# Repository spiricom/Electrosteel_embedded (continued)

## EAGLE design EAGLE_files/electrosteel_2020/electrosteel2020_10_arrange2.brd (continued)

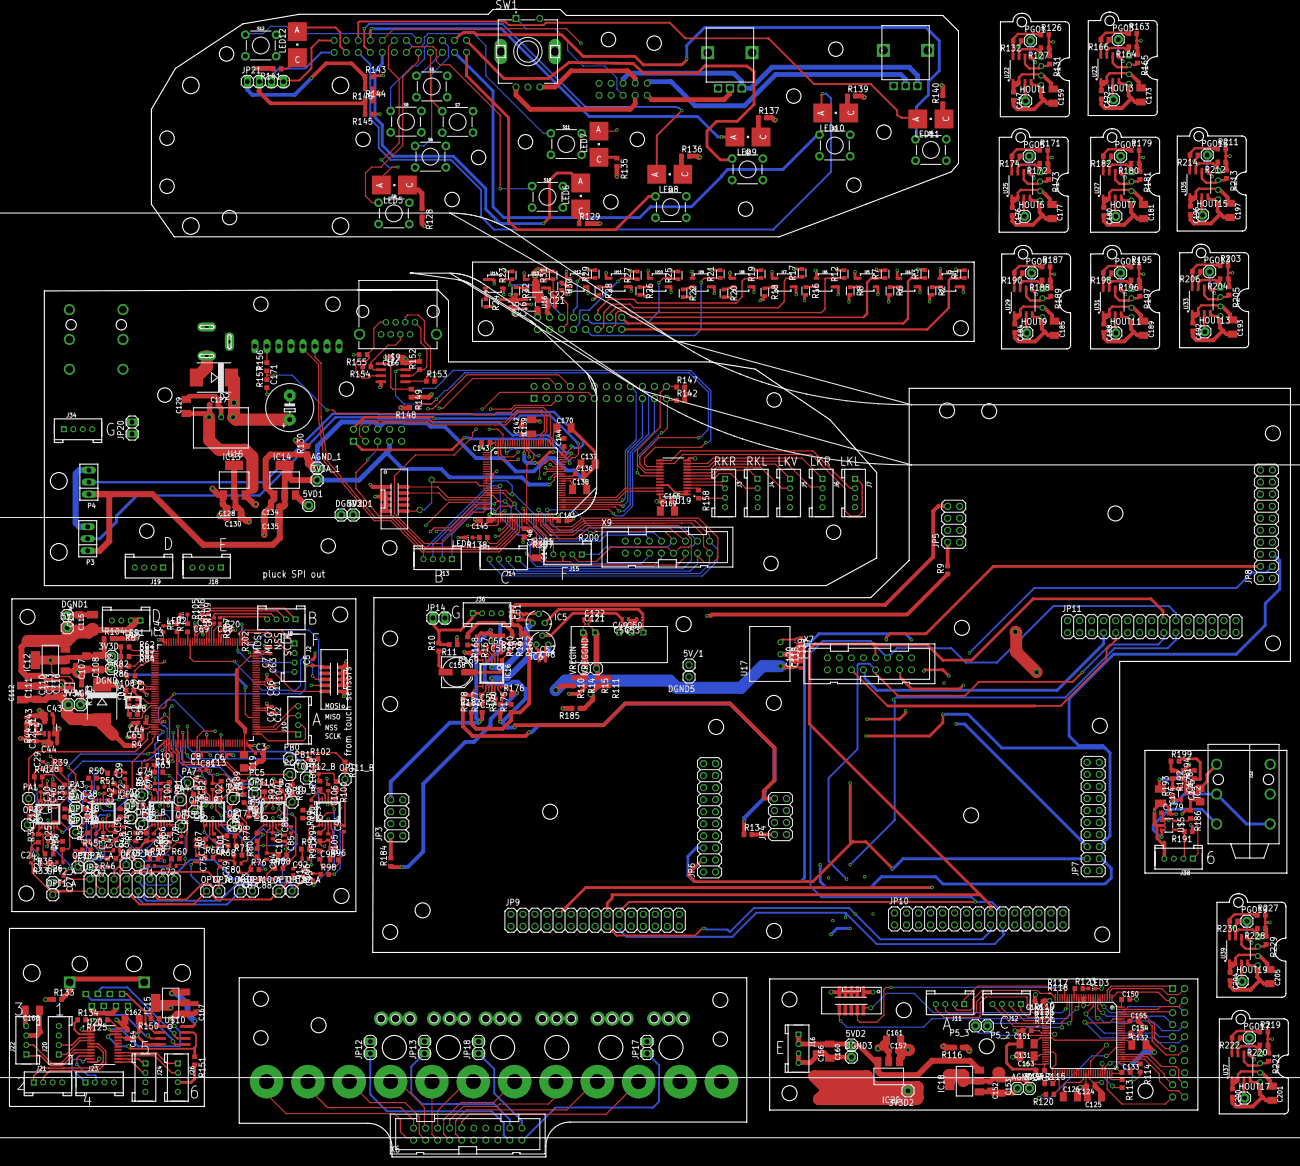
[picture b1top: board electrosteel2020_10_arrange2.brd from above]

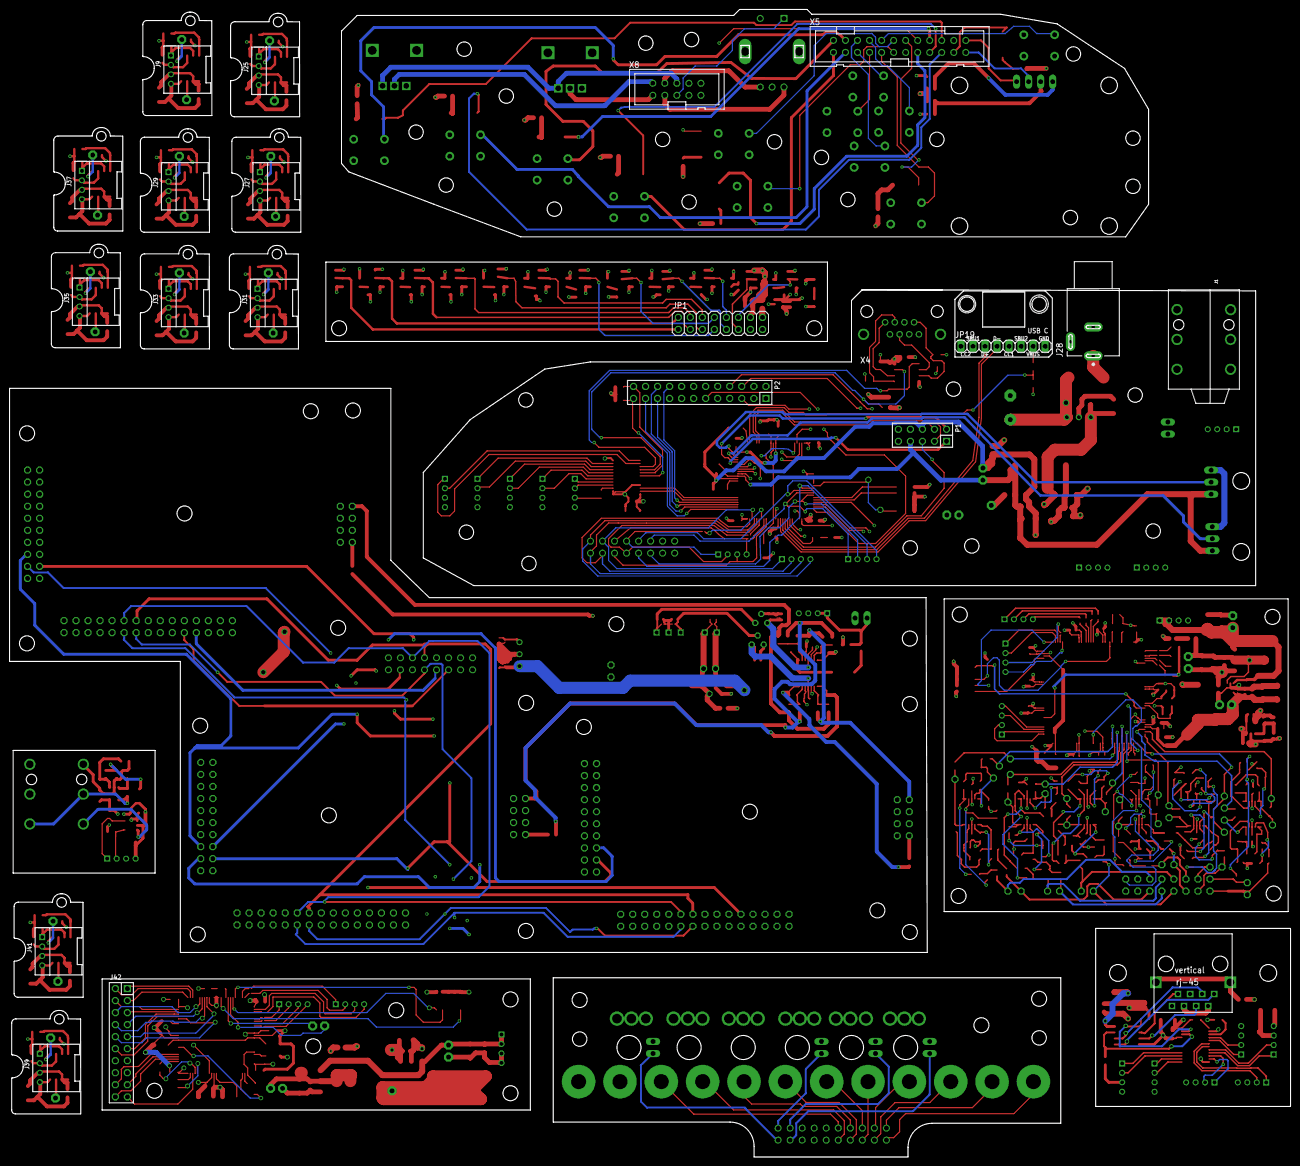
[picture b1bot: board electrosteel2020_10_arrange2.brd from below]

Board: 4 copper layers, 270.5 x 242.3 mm, 643 parts (21 on the bottom side), 495 nets.

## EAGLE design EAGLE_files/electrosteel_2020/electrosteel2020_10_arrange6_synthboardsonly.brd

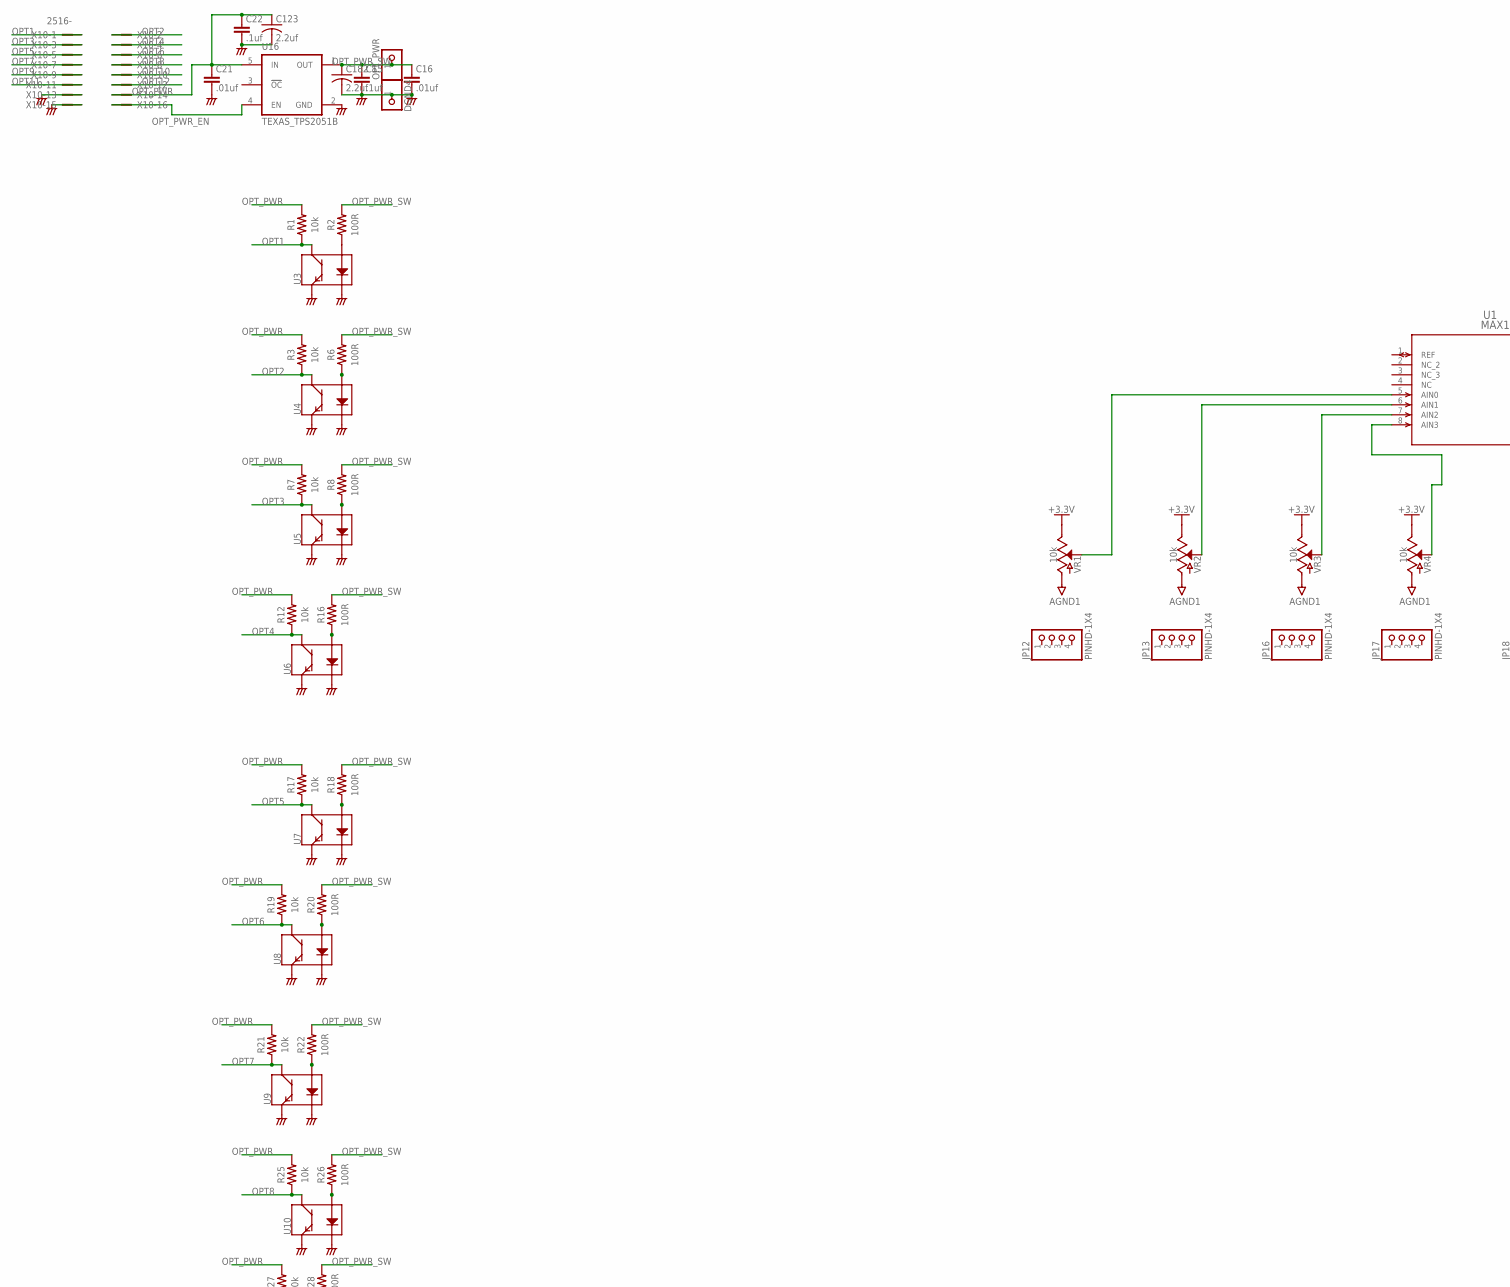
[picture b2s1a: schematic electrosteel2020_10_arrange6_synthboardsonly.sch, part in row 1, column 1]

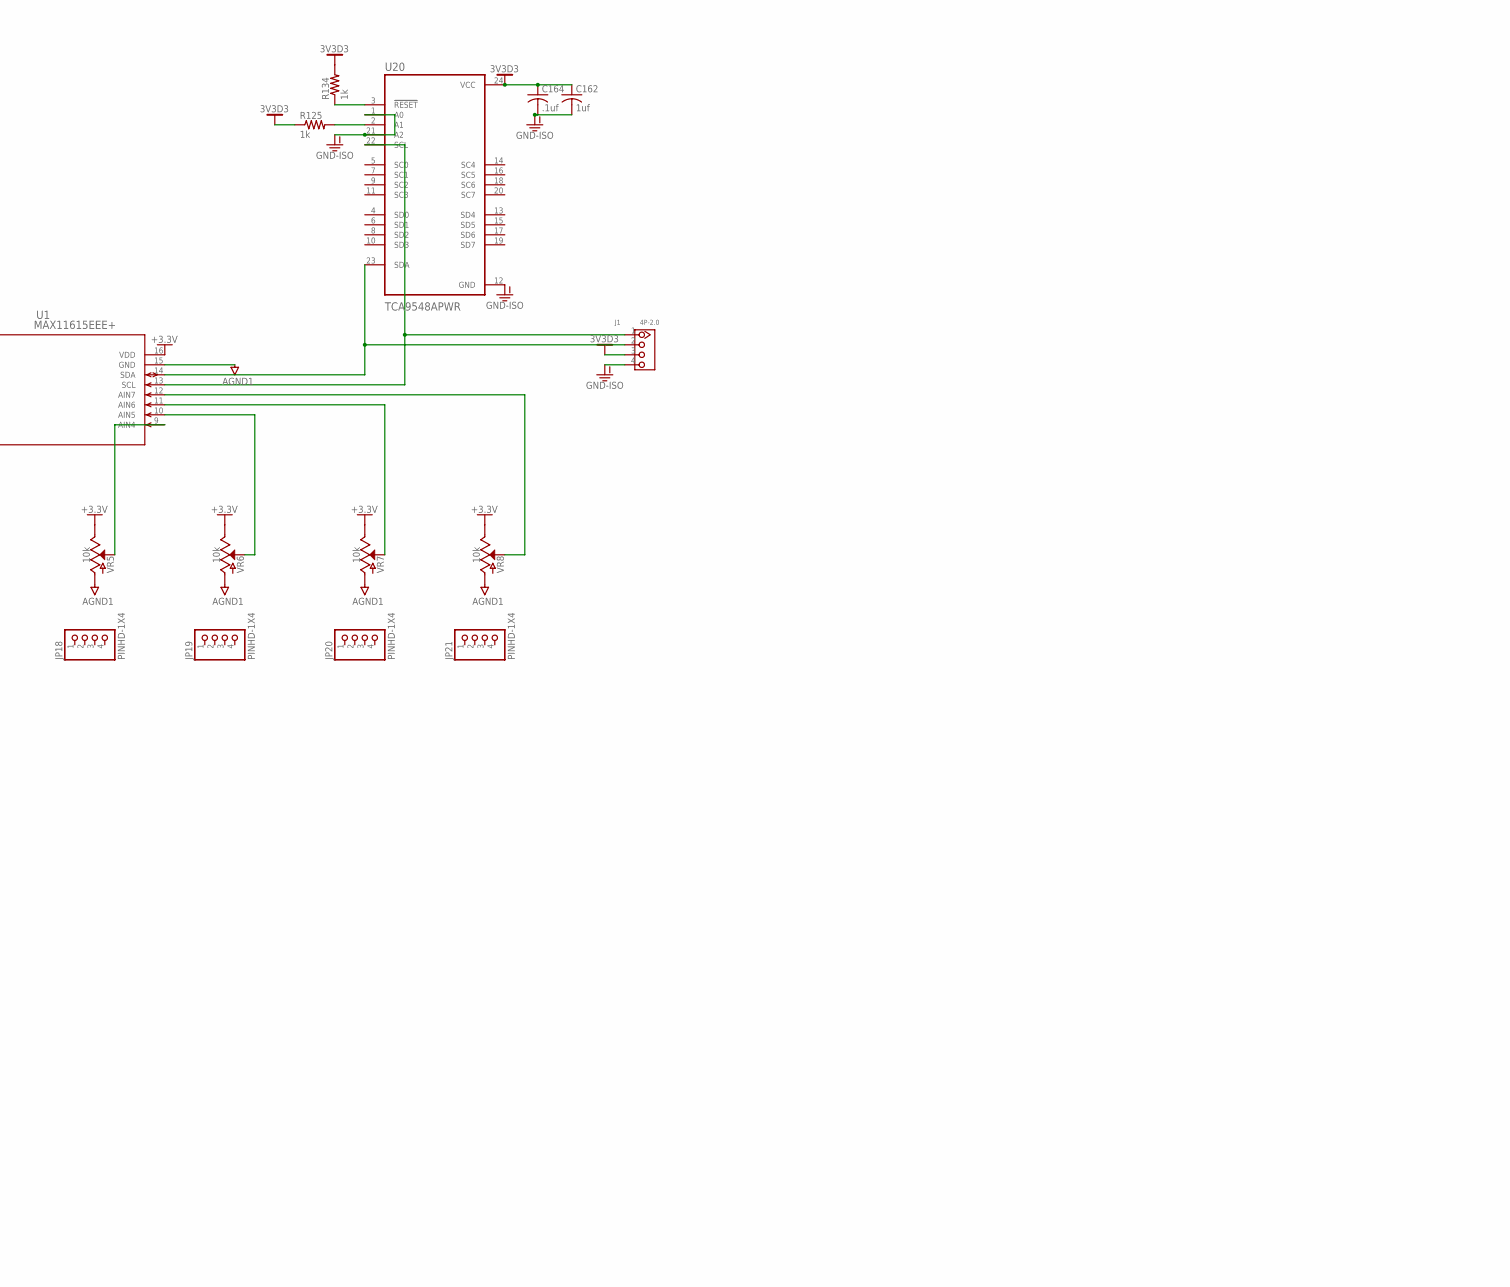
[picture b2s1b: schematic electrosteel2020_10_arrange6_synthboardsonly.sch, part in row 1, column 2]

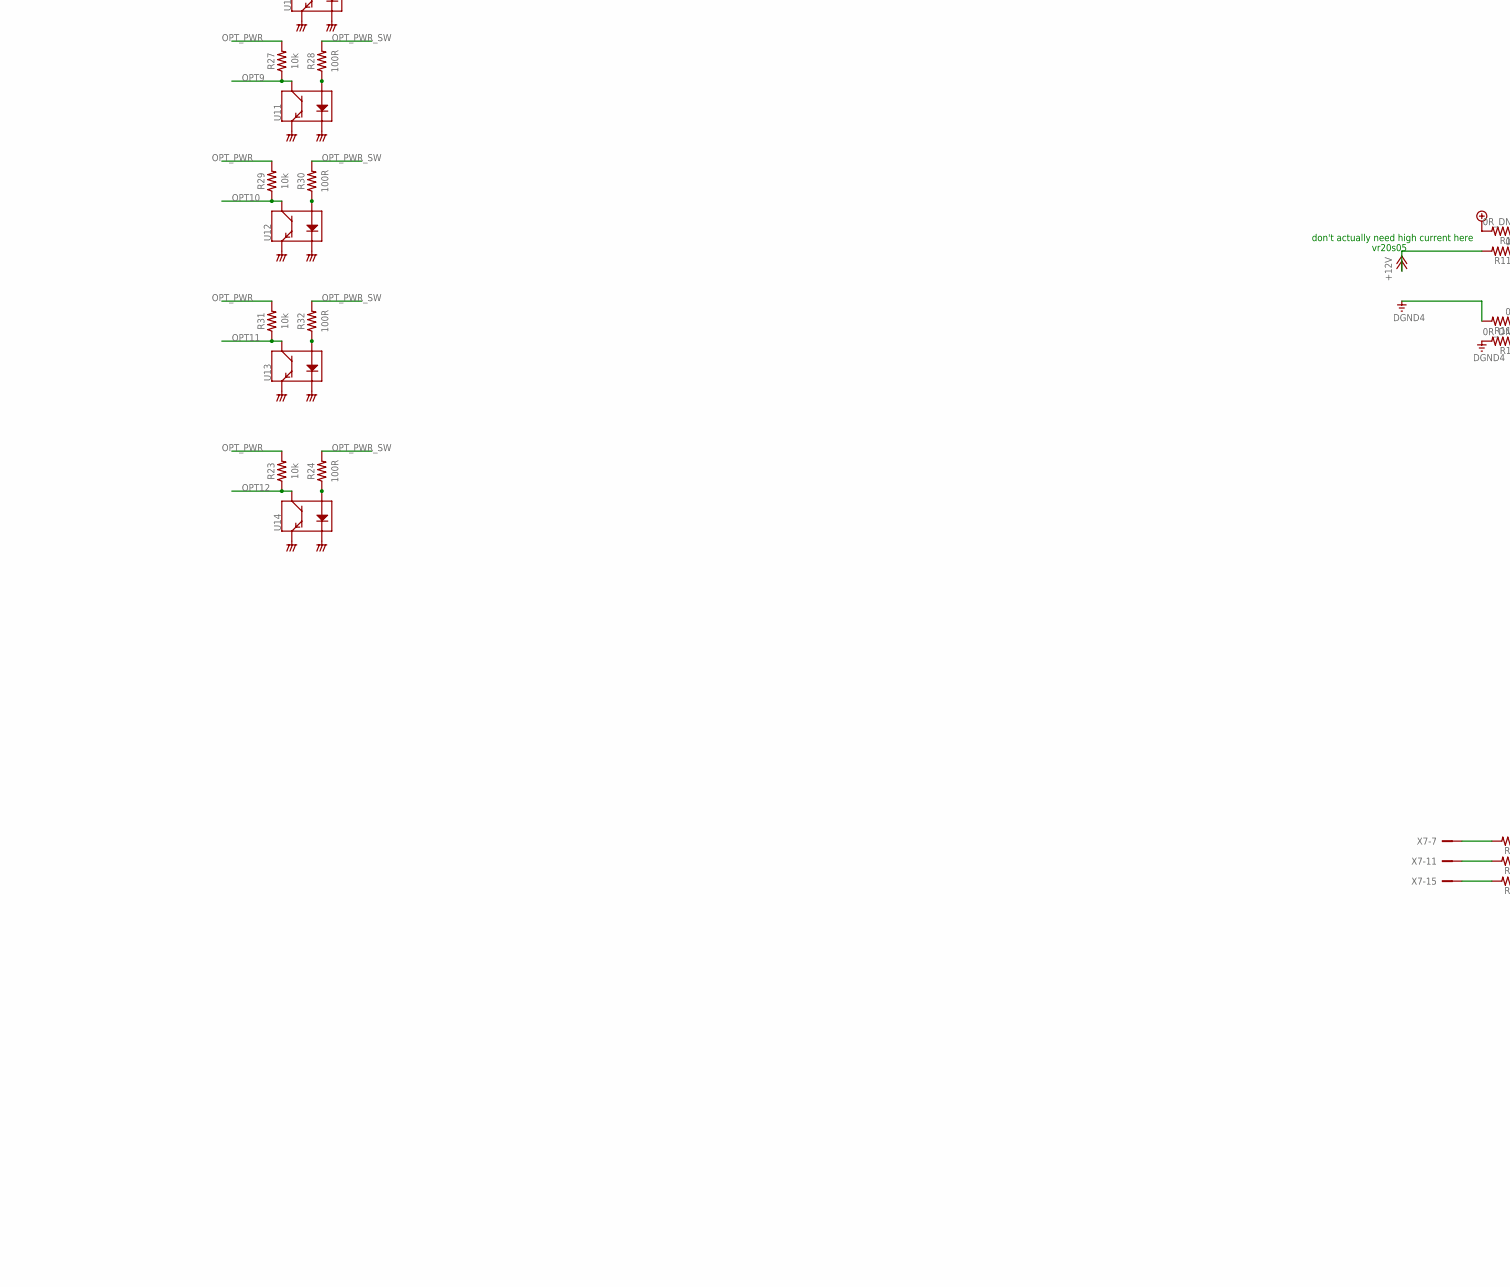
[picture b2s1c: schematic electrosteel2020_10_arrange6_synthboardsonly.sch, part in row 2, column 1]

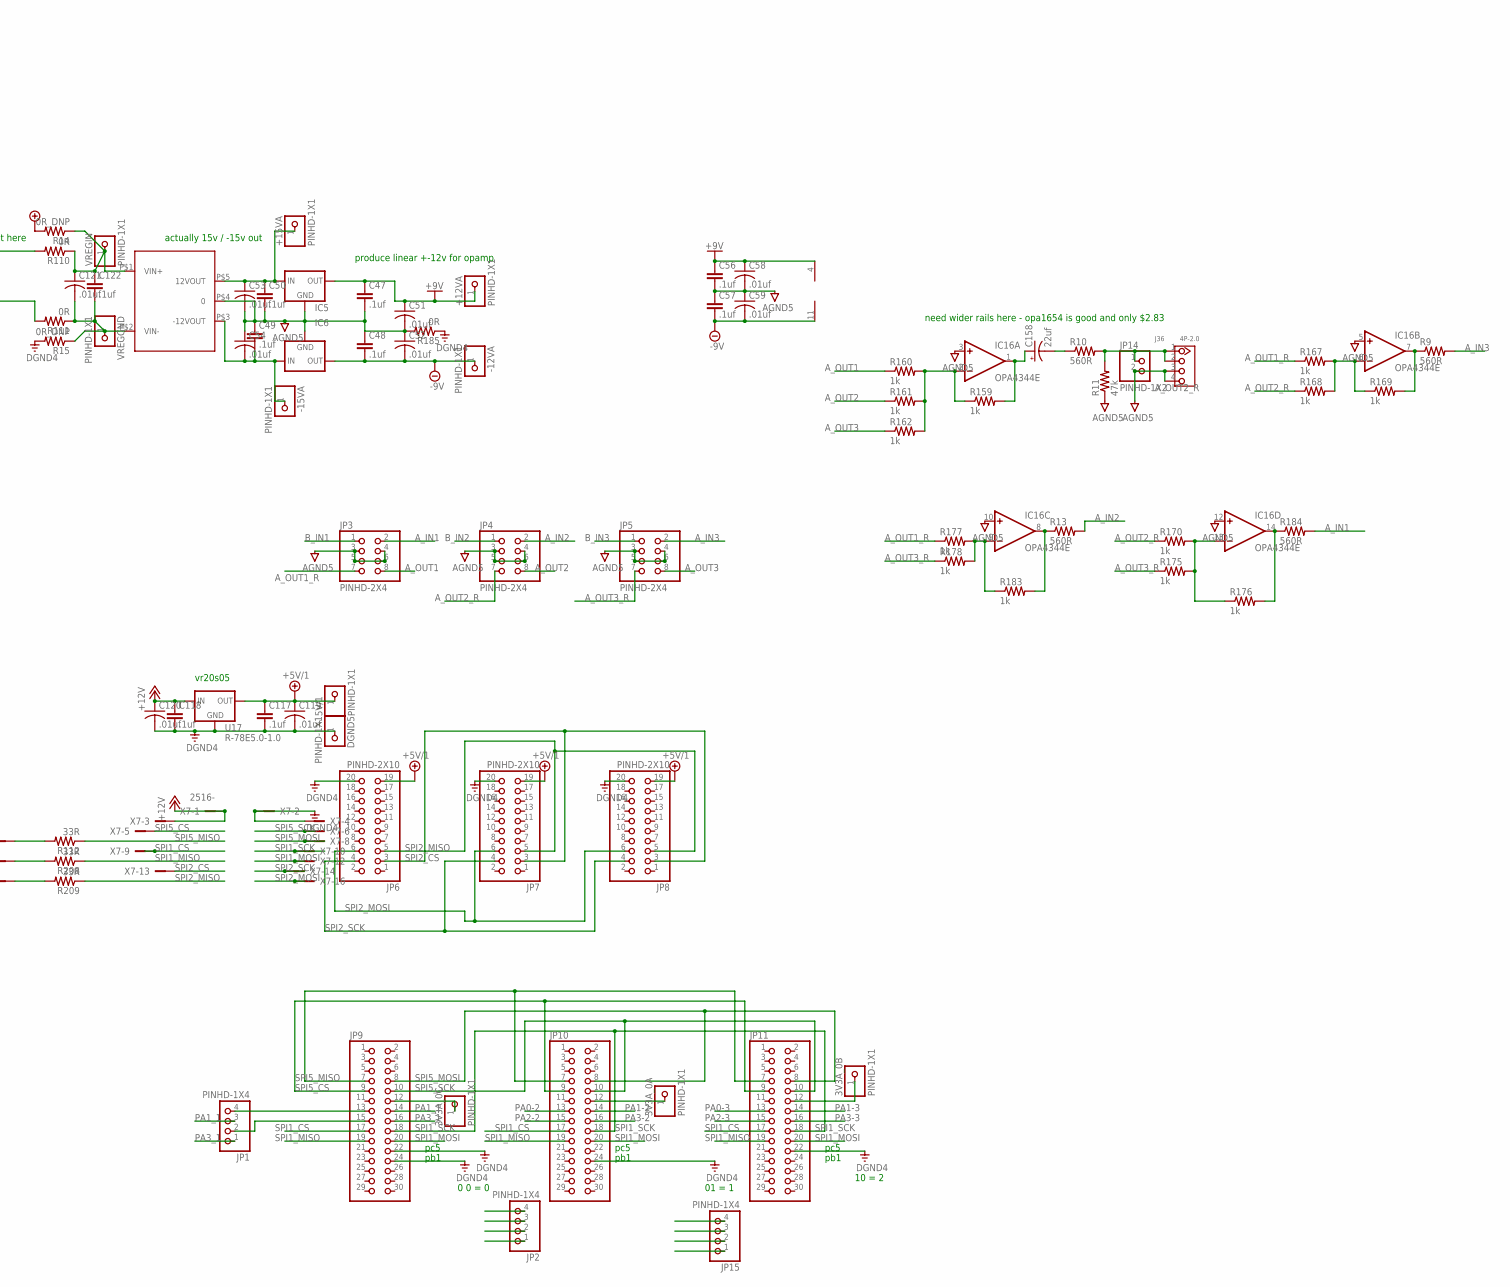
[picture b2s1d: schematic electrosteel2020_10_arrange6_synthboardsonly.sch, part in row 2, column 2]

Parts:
3V3A_0A, 3V3A_0B, 3V3A_0C, 5V/1: PINHD-1X1; 1X01; PARTNO *DNP
+12VA, +15VA: PINHD-1X1; 1X01; PARTNO *DNP
-12VA, -15VA: PINHD-1X1; 1X01; PARTNO *DNP
C15, C22, C47, C48, C49, C50, C56, C57, C117, C118, C122: .1uf; 0402; PARTNO CC0402KRX7R8BB104
C16, C21: .01uf; 0402; PARTNO CC0402KRX7R8BB103
C51, C52, C53, C54, C58, C59, C119, C120, C121: .01uf; C0201; PARTNO TMK063B7103KP-F
C123, C182: 2.2uf; C1206; PARTNO T491A225K020AT
C158: 22uf; PANASONIC_D; PARTNO EEE-1CA220NP
C162: 1uf; C1206K; PARTNO C3216X7R1E105K085AA
C164: .1uf; C0603K; PARTNO CC0603KRX7R8BB104
DGND4, DGND5: PINHD-1X1; 1X01; PARTNO *DNP
IC5: 78LXX; PARTNO LM78L12ACZ/LFT7
IC6: 79LXX; PARTNO L79L12ACZ-TR
IC16: OPA4344E; TSSOP14; PARTNO OPA1654AIPWR
J1, J36: 4P-2.0; HW4-2.0; PARTNO 110990030
JP1, JP2, JP12, JP13, JP15, JP16, JP17, JP18, JP19, JP20, JP21: PINHD-1X4; 1X04
JP3, JP4, JP5: PINHD-2X4; 2X04; PARTNO 77313-101-08LF
JP6, JP7, JP8: PINHD-2X10; 2X10; PARTNO 77313-101-20LF
JP9, JP10, JP11: PINHD-2X15; 2X15; PARTNO 77313-101-30LF
JP14: PINHD-1X2; 1X02; PARTNO *DNP
OPT_PWR: PINHD-1X1; 1X01; PARTNO *DNP
R1, R3, R7, R12, R17, R19, R21, R23, R25, R27, R29, R31: 10k; RESC1608X60; PARTNO ESR03EZPF1002
R2, R6, R8, R16, R18, R20, R22, R24, R26, R28, R30, R32: 100R; RESC1608X60; PARTNO ESR03EZPJ101
R9, R10, R13, R184: 560R; R0603; PARTNO ESR03EZPF5600
R11: 47k; R0603; PARTNO ESR03EZPJ473
R14, R15: 0R_DNP; R0603; PARTNO *DNP
R110, R111, R185: 0R; R0603; PARTNO RCS06030000Z0EA
R112, R208, R209: 33R; R0201; PARTNO RC0201FR-0733RL
R125, R134, R159, R160, R161, R162, R167, R168, R169, R170, R175, R176, R177, R178, R183: 1k; R0603; PARTNO ESR03EZPF1001
U1: MAX11615EEE+; 21-0055H_16_MXM
U3, U4, U5, U6, U7, U8, U9, U10, U11, U12, U13, U14: QRE1113; PARTNO QRE1113GR
U16: TEXAS_TPS2051B; TEXAS_SOT23-5; PARTNO TPS2051BDBVRG4
U17: R-78E5.0-1.0; DC-DC_CONVERTER_78XX; PARTNO R-78E5.0-1.0
U20: TCA9548APWR; SOP65P640X120-24N; PARTNO TCA9548APWR
U$3: CMR0512S3C; PARTNO DPU01M-15
VR1, VR2, VR3, VR4, VR5, VR6, VR7, VR8: 10k; POT-PTH-ALPS
VREGGND: PINHD-1X1; 1X01; PARTNO *DNP
VREGIN: PINHD-1X1; 1X01; PARTNO *DNP
X7, X10: 2516-; PAK100/2500-16; PARTNO D2516-6002-AR

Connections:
3V3D3: C162.1, C164.1, J1.3, R125.1, R134.2, U20.24 (VCC)
+3.3V: U1.16 (VDD), VR1.P$1 (E), VR2.P$1 (E), VR3.P$1 (E), VR4.P$1 (E), VR5.P$1 (E), VR6.P$1 (E), VR7.P$1 (E), VR8.P$1 (E)
+5V/1: 5V/1.1, C117.1, C119.1, JP6.19, JP7.19, JP8.19, R14.2, U17.VOUT (OUT)
+9V: +12VA.1, C47.1, C51.1, C56.1, C58.1, IC5.OUT, IC16.4 (V+)
+12V: C118.1, C120.1, R110.2, U17.VIN (IN), X7.1, X7.3
-9V: -12VA.1, C48.2, C52.2, C57.2, C59.2, IC6.OUT, IC16.11 (V-)
AGND1: U1.15 (GND), VR1.P$3 (A), VR2.P$3 (A), VR3.P$3 (A), VR4.P$3 (A), VR5.P$3 (A), VR6.P$3 (A), VR7.P$3 (A), VR8.P$3 (A)
AGND5: C47.2, C48.1, C49.1, C50.2, C51.2, C52.1, C53.2, C54.1, C56.2, C57.1, C58.2, C59.1, IC5.GND, IC6.GND, IC16.3 (+IN), IC16.5 (+IN), IC16.10 (+IN), IC16.12 (+IN), J36.3, J36.4, JP3.3, JP3.4, JP3.5, JP3.6, JP4.3, JP4.4, JP4.5, JP4.6, JP5.3, JP5.4, JP5.5, JP5.6, JP14.2, R11.1, R185.2, U$3.P$4 (0)
A_IN1: JP3.2, R184.2
A_IN2: JP4.2, R13.2
A_IN3: JP5.2, R9.2
A_OUT1: JP3.8, R160.1
A_OUT1_R: JP3.7, R167.1, R177.1
A_OUT2: JP4.8, R161.1
A_OUT2_R: JP4.7, R168.1, R170.1
A_OUT3: JP5.8, R162.1
A_OUT3_R: JP5.7, R175.1, R178.1
B_IN1: JP3.1
B_IN2: JP4.1
B_IN3: JP5.1
CGND: C15.2, C16.2, C21.2, C22.2, C123.2, C182.2, DGND4.1, U3.2 (K), U3.4 (E), U4.2 (K), U4.4 (E), U5.2 (K), U5.4 (E), U6.2 (K), U6.4 (E), U7.2 (K), U7.4 (E), U8.2 (K), U8.4 (E), U9.2 (K), U9.4 (E), U10.2 (K), U10.4 (E), U11.2 (K), U11.4 (E), U12.2 (K), U12.4 (E), U13.2 (K), U13.4 (E), U14.2 (K), U14.4 (E), U16.2 (GND), X10.13, X10.15
DGND4: C117.2, C118.2, C119.2, C120.2, DGND5.1, JP6.20, JP7.20, JP8.20, JP9.22, JP9.24, JP10.24, JP11.22, R15.2, R111.2, R185.1, U17.GND, X7.2, X7.4
GND-ISO: C162.2, C164.2, J1.4, U20.1 (A0), U20.12 (GND), U20.21 (A2)
unnamed: R6.1, U4.1 (A)
unnamed: R2.1, U3.1 (A)
unnamed: U1.5 (AIN0), VR1.P$2 (S)
unnamed: U1.6 (AIN1), VR2.P$2 (S)
unnamed: U1.7 (AIN2), VR3.P$2 (S)
unnamed: U1.8 (AIN3), VR4.P$2 (S)
unnamed: R8.1, U5.1 (A)
unnamed: U1.9 (AIN4), VR5.P$2 (S)
unnamed: U1.10 (AIN5), VR6.P$2 (S)
unnamed: IC16.6 (-IN), R167.2, R168.2, R169.1
unnamed: U1.11 (AIN6), VR7.P$2 (S)
unnamed: U1.12 (AIN7), VR8.P$2 (S)
unnamed: J1.2, U1.14 (SDA), U20.23 (SDA)
unnamed: J1.1, U1.13 (SCL), U20.22 (SCL)
unnamed: R125.2, U20.2 (A1)
unnamed: IC16.2 (-IN), R159.1, R160.2, R161.2, R162.2
unnamed: IC16.7 (OUT), R9.1, R169.2
unnamed: IC16.9 (-IN), R177.2, R178.2, R183.1
unnamed: +15VA.1, C50.1, C53.1, IC5.IN, U$3.P$5 (12VOUT)
unnamed: C158.+, IC16.1 (OUT), R159.2
unnamed: R16.1, U6.1 (A)
unnamed: -15VA.1, C49.2, C54.2, IC6.IN, U$3.P$3 (-12VOUT)
unnamed: R18.1, U7.1 (A)
unnamed: R20.1, U8.1 (A)
unnamed: R22.1, U9.1 (A)
unnamed: R24.1, U14.1 (A)
unnamed: R26.1, U10.1 (A)
unnamed: R28.1, U11.1 (A)
unnamed: R30.1, U12.1 (A)
unnamed: R32.1, U13.1 (A)
unnamed: C121.2, C122.2, R15.1, R111.1, U$3.P$2 (VIN-), VREGGND.1
unnamed: C121.1, C122.1, R14.1, R110.1, U$3.P$1 (VIN+), VREGIN.1
unnamed: R134.1, U20.3 (!RESET)
unnamed: IC16.8 (OUT), R13.1, R183.2
unnamed: C158.-, R10.1
unnamed: IC16.14 (OUT), R176.2, R184.1
unnamed: IC16.13 (-IN), R170.2, R175.2, R176.1
unnamed: J36.1, J36.2, JP14.1, R10.2, R11.2
unnamed: R209.2, X7.15
unnamed: R208.2, X7.11
unnamed: R112.2, X7.7
unnamed: JP1.4, JP9.13
unnamed: 3V3A_0C.1, JP9.12
unnamed: JP1.2, JP9.15
unnamed: 3V3A_0A.1, JP10.12
unnamed: 3V3A_0B.1, JP11.12
OPT1: R1.1, U3.3 (C), X10.1
OPT2: R3.1, U4.3 (C), X10.2
OPT3: R7.1, U5.3 (C), X10.3
OPT4: R12.1, U6.3 (C), X10.4
OPT5: R17.1, U7.3 (C), X10.5
OPT6: R19.1, U8.3 (C), X10.6
OPT7: R21.1, U9.3 (C), X10.7
OPT8: R25.1, U10.3 (C), X10.8
OPT9: R27.1, U11.3 (C), X10.9
OPT10: R29.1, U12.3 (C), X10.10
OPT11: R31.1, U13.3 (C), X10.11
OPT12: R23.1, U14.3 (C), X10.12
OPT_PWR: C21.1, C22.1, C123.1, R1.2, R3.2, R7.2, R12.2, R17.2, R19.2, R21.2, R23.2, R25.2, R27.2, R29.2, R31.2, U16.5 (IN), X10.14
OPT_PWR_EN: U16.4 (EN), X10.16
OPT_PWR_SW: C15.1, C16.1, C182.1, OPT_PWR.1, R2.2, R6.2, R8.2, R16.2, R18.2, R20.2, R22.2, R24.2, R26.2, R28.2, R30.2, R32.2, U16.1 (OUT)
PA0-2: JP2.4, JP10.13
PA0-3: JP11.13, JP15.4
PA1-2: JP2.3, JP10.14
PA1-3: JP11.14, JP15.3
PA1_1: JP1.3, JP9.14
PA2-2: JP2.2, JP10.15
PA2-3: JP11.15, JP15.2
PA3-2: JP2.1, JP10.16
PA3-3: JP11.16, JP15.1
PA3_1: JP1.1, JP9.16
SPI1_CS: JP9.17, JP10.17, JP11.17, X7.9
SPI1_MISO: JP9.19, JP10.19, JP11.19, R208.1
SPI1_MOSI: JP9.20, JP10.20, JP11.20, X7.12
SPI1_SCK: JP9.18, JP10.18, JP11.18, X7.10
SPI2_CS: JP6.3, JP7.3, JP8.3, X7.13
SPI2_MISO: JP6.5, JP7.5, JP8.5, R209.1
SPI2_MOSI: JP6.6, JP7.6, JP8.6, X7.16
SPI2_SCK: JP6.4, JP7.4, JP8.4, X7.14
SPI5_CS: JP9.9, JP10.9, JP11.9, X7.5
SPI5_MISO: JP9.7, JP10.7, JP11.7, R112.1
SPI5_MOSI: JP9.8, JP10.8, JP11.8, X7.8
SPI5_SCK: JP9.10, JP10.10, JP11.10, X7.6

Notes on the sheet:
produce linear +-12v for opamp
vr20s05
0 0 = 0
01 = 1
10 = 2
don't actually need high current here
pc5
pb1
need wider rails here - opa1654 is good and only $2.83
actually 15v / -15v out

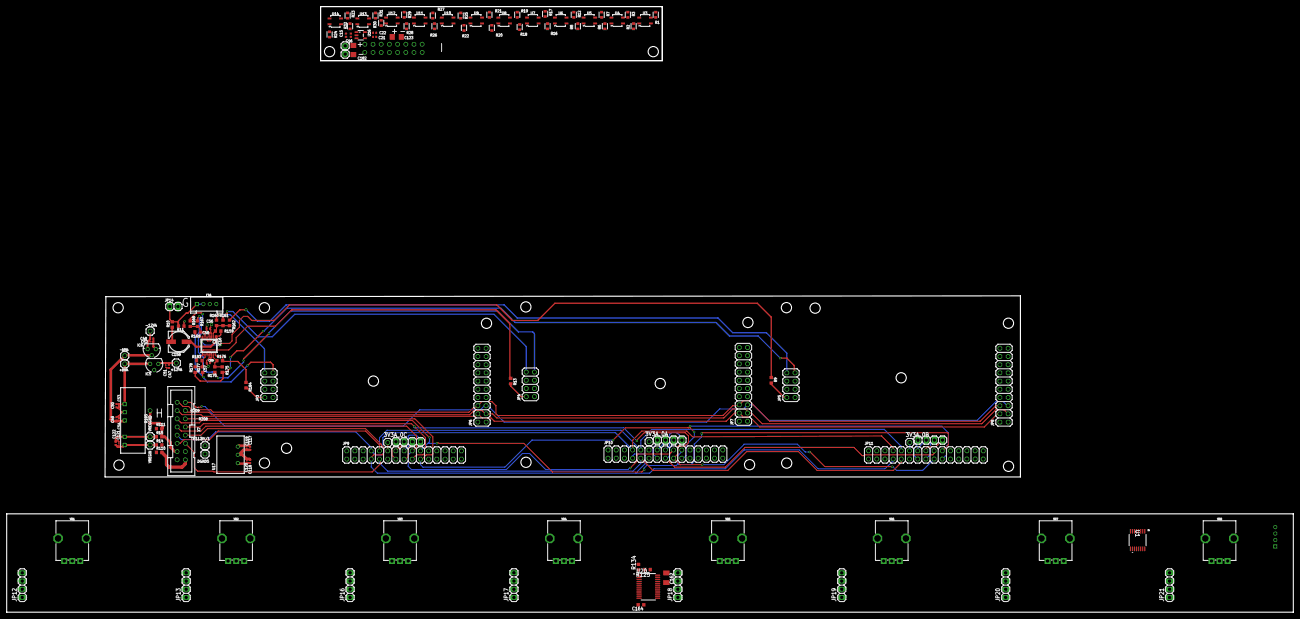
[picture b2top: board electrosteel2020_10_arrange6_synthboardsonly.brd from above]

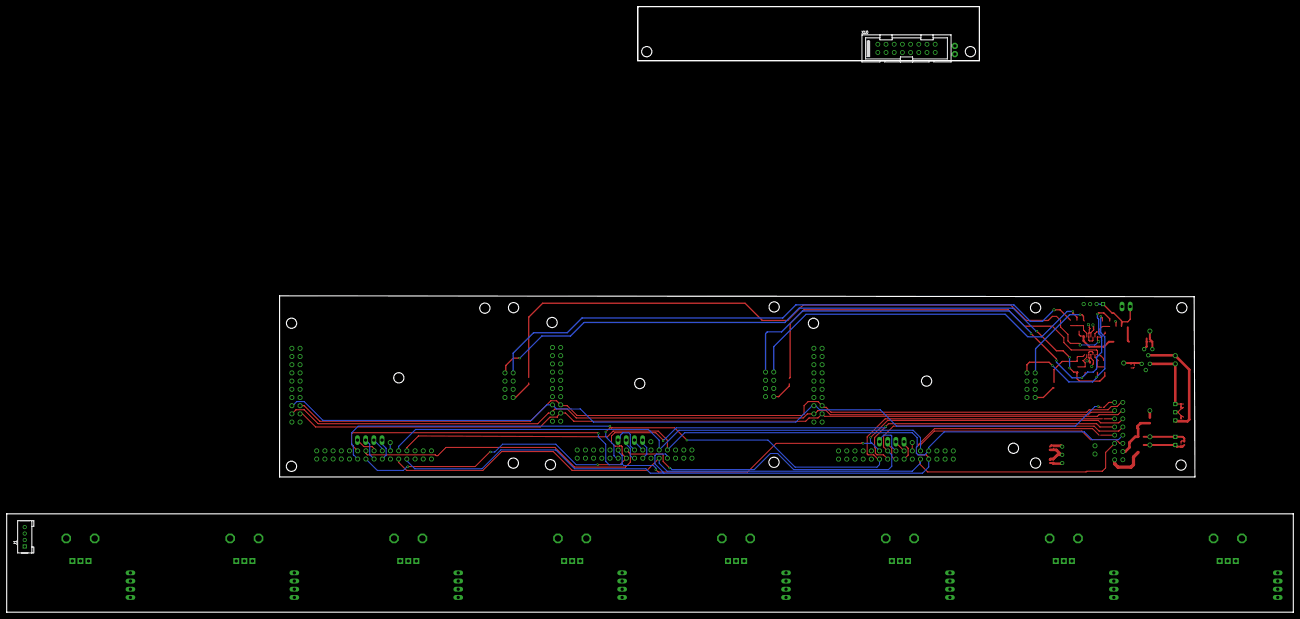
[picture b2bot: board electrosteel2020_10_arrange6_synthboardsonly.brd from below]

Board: 4 copper layers, 398.8 x 187.7 mm, 145 parts (2 on the bottom side), 103 nets.

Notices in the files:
parts and their libraries:
SparkFun-IC-Microcontroller: Licensing: Creative Commons ShareAlike 4.0 International - https://creativecommons.org/licenses/by-sa/4.0
con-headers-jp: Copyright (C) 2008, Bob Starr
